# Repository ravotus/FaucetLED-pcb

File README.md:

# FaucetLED-pcb
PCB for the [FaucetLED](https://github.com/ravotus/FaucetLED) project.

Created with KiCad 4.0.5. Available through OSHPark: [https://oshpark.com/shared_projects/xyDQwA8Q](https://oshpark.com/shared_projects/xyDQwA8Q)

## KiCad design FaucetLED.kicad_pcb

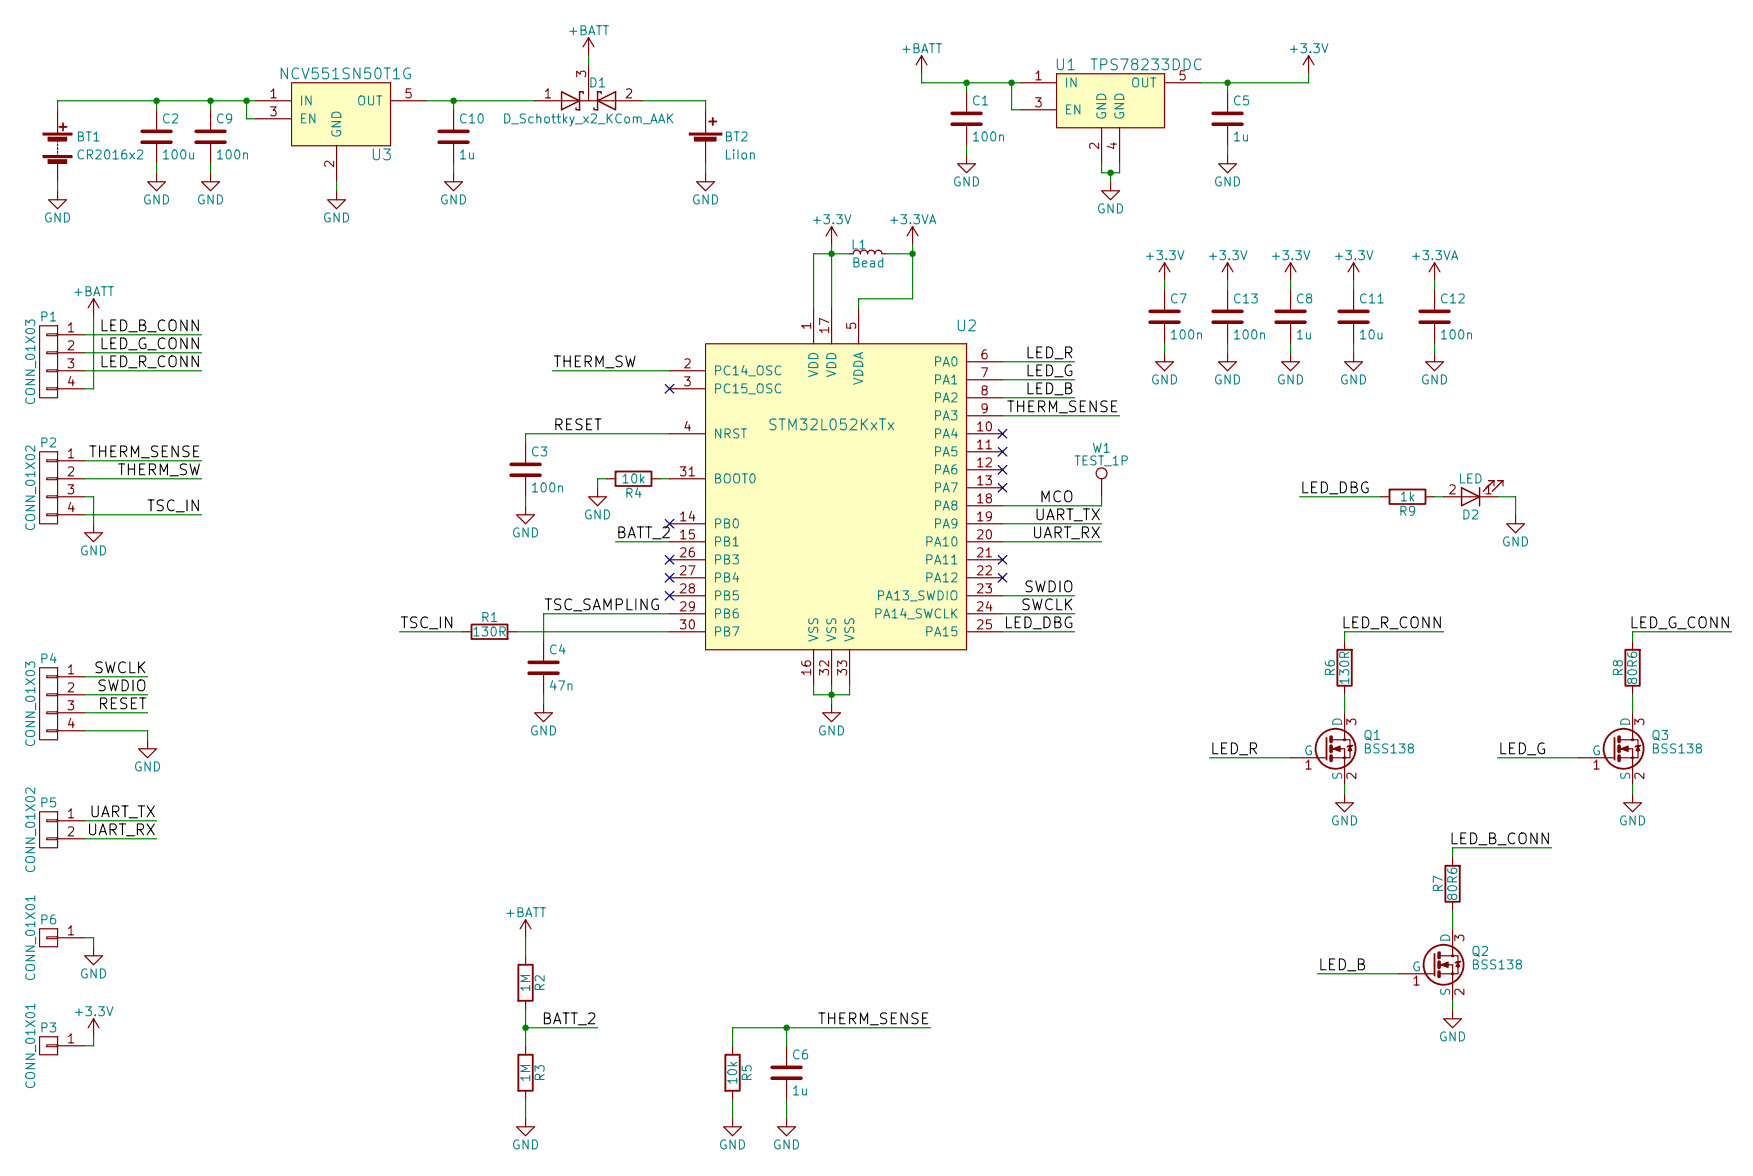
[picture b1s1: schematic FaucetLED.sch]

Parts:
BT1: CR2016x2; Keystone_3020_2x2016-CoinCell; Manufacturer PN 3020; DigiKey PN 36-3020-ND
BT2: LiIon; JST_PH_S2B-PH-K_02x2.00mm_Angled
C1, C3, C7, C9, C12, C13: 100n; C_0603
C2: 100u; C_1210; DigiKey PN 587-4313-1-ND
C4: 47n; C_0603_0805
C5, C8, C10: 1u; C_0603
C6: 1u; C_0603_0805
C11: 10u; C_0603; DigiKey PN 587-1256-1-ND
D1: D_Schottky_x2_KCom_AAK; SOT-23; Manufacturer PN TBAT54C; DigiKey PN TBAT54CLMCT-ND
D2: LED; LED_0805; DigiKey PN 67-2191-1-ND
L1: Bead; R_0603; Manufacturer PN BK1608HW601-T; DigiKey PN 587-1879-1-ND
P1: CONN_01X03; JST_PH_S4B-PH-K_04x2.00mm_Angled
P2: CONN_01X02; JST_PH_S4B-PH-K_04x2.00mm_Angled
P3, P6: CONN_01X01; Pin_Header_Straight_1x01_Pitch2.54mm
P4: CONN_01X03; Pin_Header_Straight_1x04_Pitch2.54mm
P5: CONN_01X02; Pin_Header_Straight_1x02_Pitch2.54mm
Q1, Q2, Q3: BSS138; SOT-23
R1, R6: 130R; R_0603_0805; DigiKey PN 311-130HRCT-ND
R2, R3: 1M; R_0603_0805; DigiKey PN 311-1.00MHRCT-ND
R4, R5: 10k; R_0603_0805
R7, R8: 80R6; R_0603_0805
R9: 1k; R_0603_0805
U1: TPS78233DDC; SOT-23-5
U2: STM32L052KxTx; LQFP-32_7x7mm_Pitch0.8mm_QFN-32-1EP_5x5mm_Pitch0.5mm-Combo; Manufacturer PN STM32L052K8T6; DigiKey PN 497-14904-ND
U3: NCV551SN50T1G; SOT-23-5
W1: TEST_1P; Measurement_Point_Round-SMD-Pad_Small

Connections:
+3.3VA: C12.1, L1.2, U2.5 (VDDA)
+3V3: C5.1, C7.1, C8.1, C11.1, C13.1, L1.1, P3.1, U1.5 (OUT), U2.1 (VDD), U2.17 (VDD)
+BATT: C1.1, D1.3 (K), P1.4, R2.1, U1.1 (IN), U1.3 (EN)
/BATT_2: R2.2, R3.1, U2.15 (PB1)
/LED_B: Q2.1 (G), U2.8 (PA2)
/LED_B_CONN: P1.1, R7.2
/LED_DBG: R9.2, U2.25 (PA15)
/LED_G: Q3.1 (G), U2.7 (PA1)
/LED_G_CONN: P1.2, R8.2
/LED_R: Q1.1 (G), U2.6 (PA0)
/LED_R_CONN: P1.3, R6.2
/MCO: U2.18 (PA8), W1.1
/RESET: C3.1, P4.3, U2.4 (NRST)
/SWCLK: P4.1, U2.24 (PA14_SWCLK)
/SWDIO: P4.2, U2.23 (PA13_SWDIO)
/THERM_SENSE: C6.1, P2.1, R5.1, U2.9 (PA3)
/THERM_SW: P2.2, U2.2 (PC14_OSC)
/TSC_IN: P2.4, R1.1
/TSC_SAMPLING: C4.1, U2.29 (PB6)
/UART_RX: P5.2, U2.20 (PA10)
/UART_TX: P5.1, U2.19 (PA9)
GND: BT1.2 (-), BT2.2 (-), C1.2, C2.2, C3.2, C4.2, C5.2, C6.2, C7.2, C8.2, C9.2, C10.2, C11.2, C12.2, C13.2, D2.1 (K), P2.3, P4.4, P6.1, Q1.2 (S), Q2.2 (S), Q3.2 (S), R3.2, R4.2, R5.2, U1.2 (GND), U1.4 (GND), U2.16 (VSS), U2.32 (VSS), U2.33 (VSS), U3.2 (GND)
unnamed: BT1.1 (+), C2.1, C9.1, U3.1 (IN), U3.3 (EN)
unnamed: BT2.1 (+), D1.2 (A)
unnamed: C10.1, D1.1 (A), U3.5 (OUT)
unnamed: D2.2 (A), R9.1
unnamed: Q1.3 (D), R6.1
unnamed: Q2.3 (D), R7.1
unnamed: Q3.3 (D), R8.1
unnamed: R1.2, U2.30 (PB7)
unnamed: R4.1, U2.31 (BOOT0)

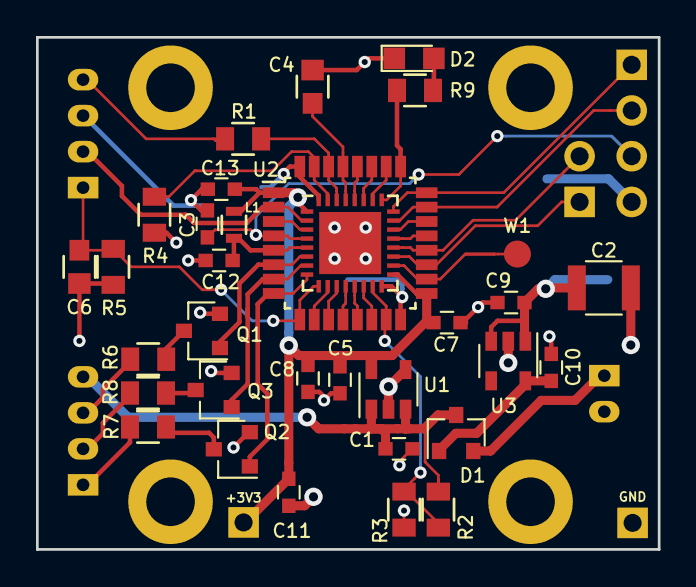
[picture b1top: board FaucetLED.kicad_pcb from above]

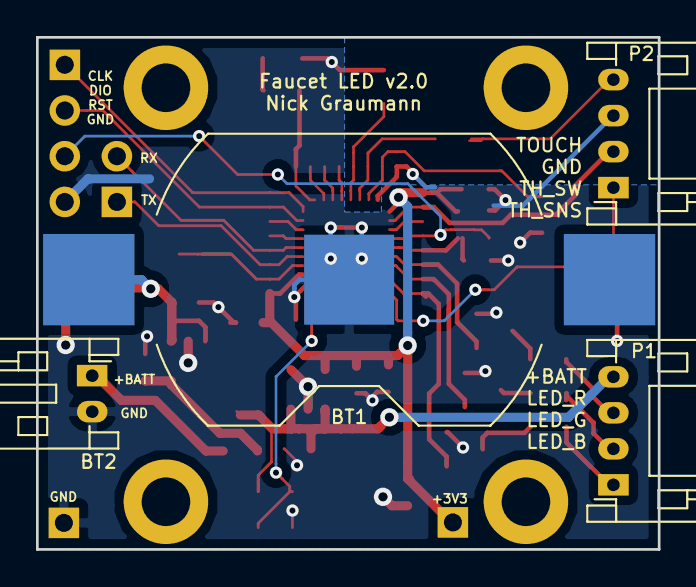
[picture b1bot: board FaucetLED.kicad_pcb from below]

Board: 2 copper layers, 34.5 x 28.4 mm, 40 parts (7 on the bottom side), 31 nets.

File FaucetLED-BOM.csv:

Reference, Quantity, Value, Footprint, Datasheet, DigiKey PN, Note, Manufacturer PN
BT1 ,1,CR2016x2,components:Keystone_3020_2x2016-CoinCell,,36-3020-ND,,3020
BT2 ,1,LiIon,Connectors_JST:JST_PH_S2B-PH-K_02x2.00mm_Angled,
C11 ,1,10u,Capacitors_SMD:C_0603,,587-1256-1-ND,,
C2 ,1,100u,Capacitors_SMD:C_1210,,587-4313-1-ND,,
C4 ,1,47n,components:C_0603_0805,
C6 ,1,100n,components:C_0603_0805,
C1 C12 C13 C3 C7 C9 ,6,100n,Capacitors_SMD:C_0603,
C10 C5 C8 ,3,1u,Capacitors_SMD:C_0603,,,Also could be 4.7uF.,
D1 ,1,D_Schottky_x2_KCom_AAK,TO_SOT_Packages_SMD:SOT-23,,TBAT54CLMCT-ND,,TBAT54C
D2 ,1,LED,LEDs:LED_0805,,67-2191-1-ND,,
L1 ,1,Bead,Resistors_SMD:R_0603,,587-1879-1-ND,,BK1608HW601-T
P1 ,1,CONN_01X03,Connectors_JST:JST_PH_S4B-PH-K_04x2.00mm_Angled,
P2 ,1,CONN_01X02,Connectors_JST:JST_PH_S4B-PH-K_04x2.00mm_Angled,
P4 ,1,CONN_01X03,Pin_Headers:Pin_Header_Straight_1x04_Pitch2.54mm,
P5 ,1,CONN_01X02,Pin_Headers:Pin_Header_Straight_1x02_Pitch2.54mm,
P3 P6 ,2,CONN_01X01,Pin_Headers:Pin_Header_Straight_1x01_Pitch2.54mm,
Q1 Q2 Q3 ,3,BSS138,TO_SOT_Packages_SMD:SOT-23,
R2 R3 ,2,1M,components:R_0603_0805,,311-1.00MHRCT-ND,,
R4 R5 ,2,10k,components:R_0603_0805,
R1 R6 ,2,130R,components:R_0603_0805,,311-130HRCT-ND,,
R7 R8 ,2,80R6,components:R_0603_0805,
R9 ,1,1k,components:R_0603_0805,
U1 ,1,TPS78233DDC,TO_SOT_Packages_SMD:SOT-23-5,
U2 ,1,STM32L052KxTx,components:LQFP-32_7x7mm_Pitch0.8mm_QFN-32-1EP_5x5mm_Pitch0.5mm-Combo,,497-14904-ND,,STM32L052K8T6
U3 ,1,NCV551SN50T1G,TO_SOT_Packages_SMD:SOT-23-5,
W1 ,1,TEST_1P,Measurement_Points:Measurement_Point_Round-SMD-Pad_Small,

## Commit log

2016-12-17 root
2016-12-17 Add Kicad project with OSH Park design rules
2016-12-18 Faucet LED v1.0 PCB complete
2016-12-19 Minor PCB tweaks to allow easier modding for MAX4257 variant
2016-12-20 Rotate amplifier circuit so piezo is on right side
2016-12-20 Rotated amplifier another 90 degrees so piezo input is in the middle
2016-12-20 Swapped LED and thermistor pins on board
2016-12-20 Minor tweaks to spacing around amp circuit
2017-01-04 Add BOM generation.
2017-02-20 WIP version 2 with STM32L0.
2017-02-20 Add battery holder, more connectors.
2017-02-20 Add part numbers for more parts.
2017-02-21 Update R and C footprints for 0603/0805 compatibility.
2017-02-21 Add mounting holes for CU-18420-B enclosure.
2017-02-22 Add 5V regulator, LED drive NMOS. Not layed out in PCB yet.
2017-02-23 More schematic tweaks to resistor values.
2017-02-23 Rotate uC to 90deg again for ease of routing.
2017-02-23 First pass of PCB layout complete. Fixed a couple incorrect ADC pins.
2017-02-23 Fix paste on both sides issue of CR2016 footprint.
2017-02-23 Move connector silkscreens to bottom of board.
2017-02-23 Fix up silkscreens to avoid overlap.
2017-02-23 Add name and version to silkscreen.
2017-02-23 Change TSC resistor to 130R for commonality. Update BOM.
2017-02-24 Fix some silkscreens for connectors.
2017-02-25 Update to Kicad 4.0.5, re-import libraries.
2017-02-25 Remove rescue library from transition.
2017-02-25 Fix coin cell holder to have GND pad in middle.
2017-02-25 Move uC up a bit for more room, increase center battery pad size.
2017-02-25 Add combo footprint for both QFN32 and LQFP32.
2017-02-25 Added more bypass caps.
2017-02-25 Move around caps for better layout.
2017-02-25 Restore accidentally deleted battery holder.
2017-02-25 Add additional bypass capacitor for other uC VCC pin.
2017-02-25 Make all bypass caps 0603, layout improvements to power and bypass.
2017-02-25 Reset cap was feeling squished, fix missing enable connection on +5V reg.
2017-02-25 Tweak position of C9 for rework, fix some silks.
2017-02-25 Add pin labels for headers, shrink all ref designators.
2017-02-25 Small schematic layout tweaks.
2017-02-26 Move C3 closer to RESET pin on uC.
2017-02-26 Silkscreen position tweaks.
2017-02-26 Update BOM.
2017-02-26 Move 100uF cap to battery input.
2017-02-26 Move BATT_2 sense R's closer to ADC input.
2017-02-26 Add footprint for another bulk cap C14 on +BATT.
2017-02-26 Change C2 and C14 to 1210 package for lower leakage.
2017-02-26 Slight move of C5 closer to 3.3V LDO.
2017-02-26 Make all 0.1uF caps 100nF, update some notes.
2017-02-27 Add some more Digikey part numbers.
2017-03-08 C4: Sampling capacitor: Change value to 0.1uF.
2017-03-08 Add mod log for v2.0 with known changes needed/wanted.
2017-03-08 Fix THERM_SENSE topology to form proper voltage divider.
2017-03-14 Remove and ignore backup files.
2017-03-14 C4: Change sampling capacitor to 47nF.
2017-03-14 U1: Change to TPS782 3.3V regulator for lower Iq.
2017-03-14 C11: Change footprint to 0603 since 1206 was unnecessary.
2017-03-14 Remove C14 (extra 100uF) since testing showed it was unnecessary.
2017-03-14 Increase text size of connector silkscreen labels.
2017-04-03 C6: Change to 1uF for <50/60Hz cutoff freq.
2017-04-03 U1: Add Digikey PN.
2017-04-04 Create LICENSE
